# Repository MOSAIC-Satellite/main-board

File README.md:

# Main Board

This is the repository for MOSAIC's Main Board.

For detailed information on the Main Board, check out its core documentation [here](https://www.mosaicsat.org/core_documentation/hardware/main_board/).

To get your own MOSAIC Main Board, visit the MOSAIC fabrication guide [here](https://www.mosaicsat.org/getting_mosaic/).

## Current Features

*Newest board version: 1.0*

| **Feature** |
| :----------- |
| Swappable Processor Slot |
| 2x Expandable Memory Slots |
| 2x Function Board Slots |
| USB/Battery Voltage Regulator |
| Qwiic Voltage Regulator |
| Built-in Resettable PTC Fuse |
| 2-Pin JST Connector |
| Single Cell LiPo Charge Circuit |
| USB Type C Connector |
| 2x Qwiic Connectors |
| SWD 2x5 Header |
| Multiplexer for UART1  |
| Boot and Reset Buttons |
| 3x I/O switches |

## Planned Changes

The following are the current plans for changes to MOSAIC's Main Board. 

- Remove one of the expandable memory slots and replace it with a permanent SD card slot. This means that those interested only in SD cards for memory storage don't need a separate PCB to add to the board. 

## Change Log

You can find the change log for the Main Board on MOSAIC's website [here](https://www.mosaicsat.org/core_documentation/hardware/main_board/change_log/).

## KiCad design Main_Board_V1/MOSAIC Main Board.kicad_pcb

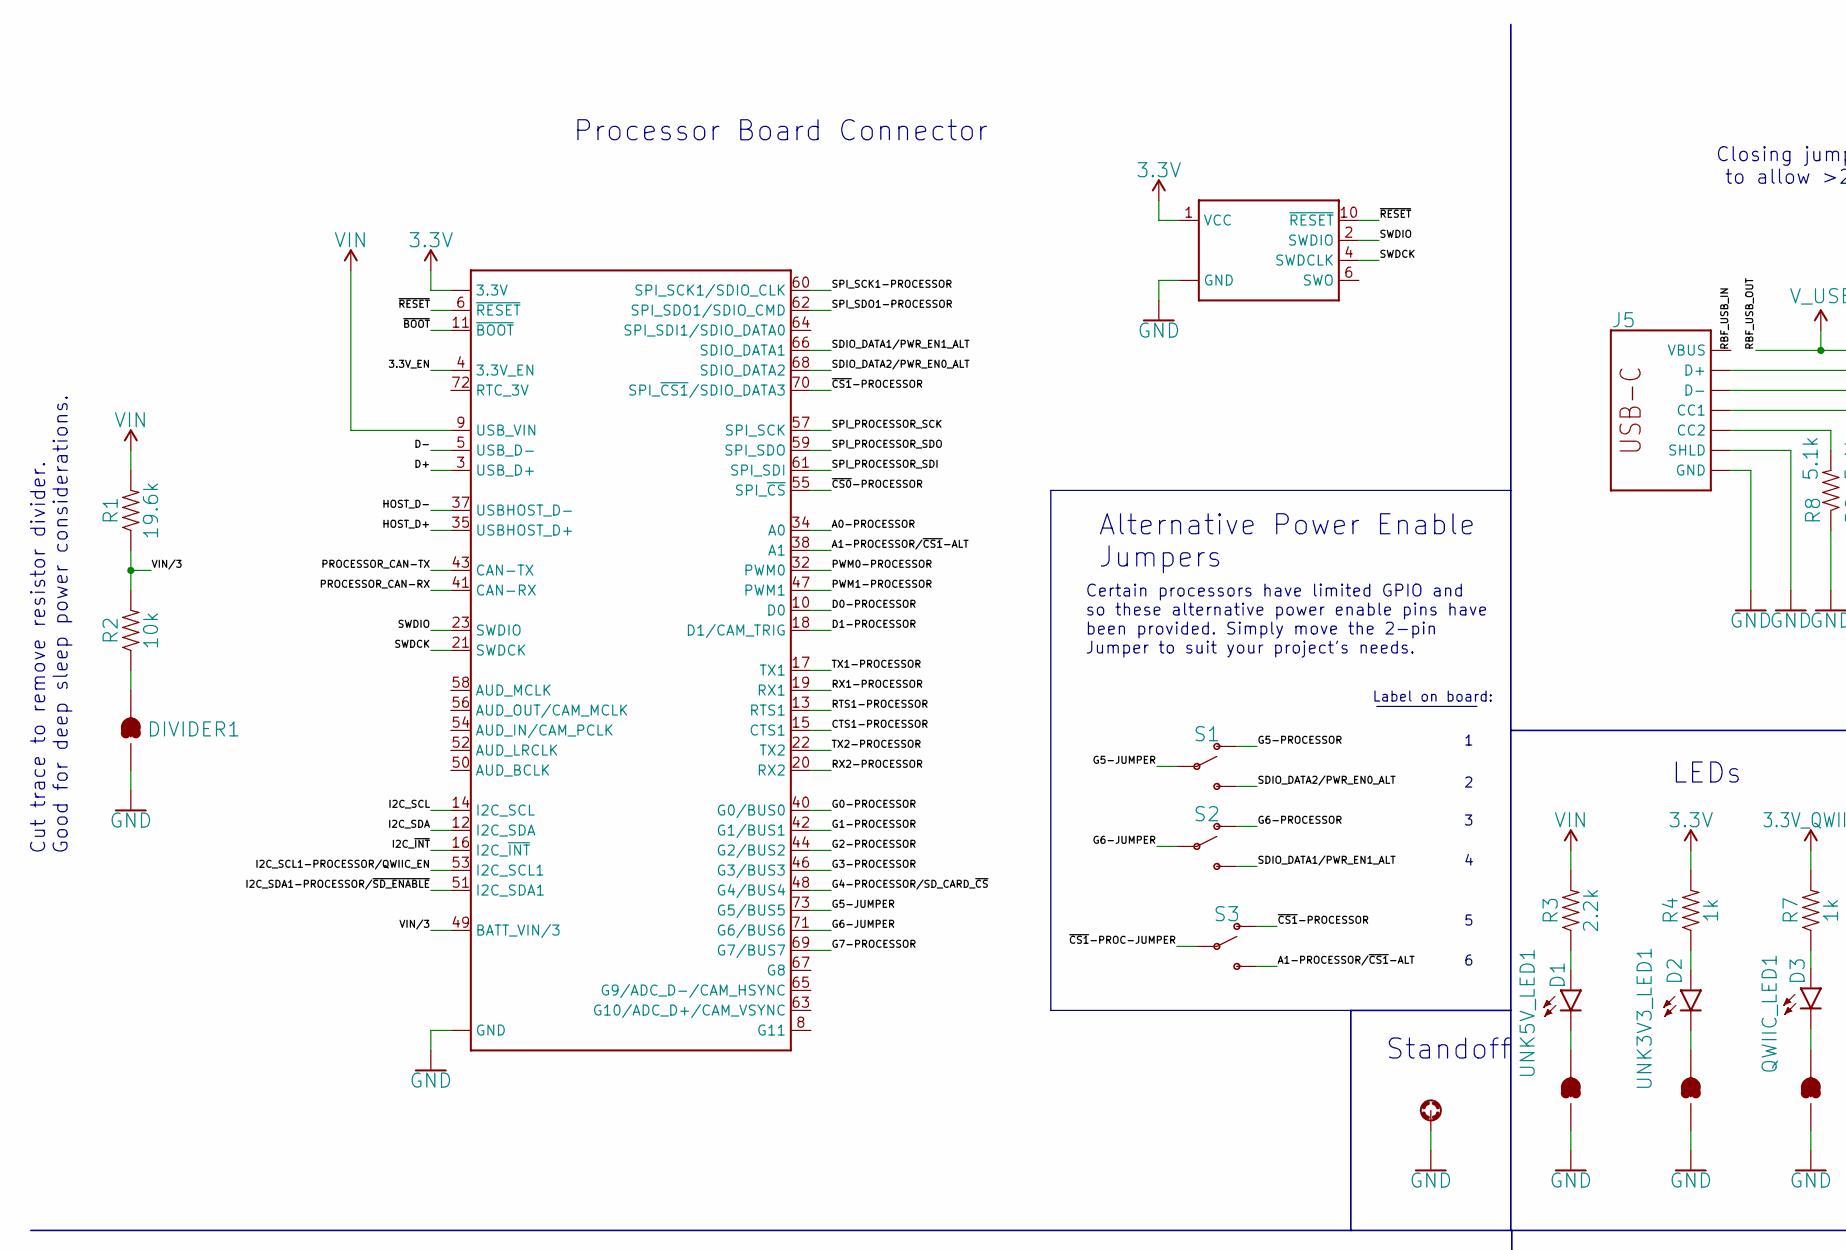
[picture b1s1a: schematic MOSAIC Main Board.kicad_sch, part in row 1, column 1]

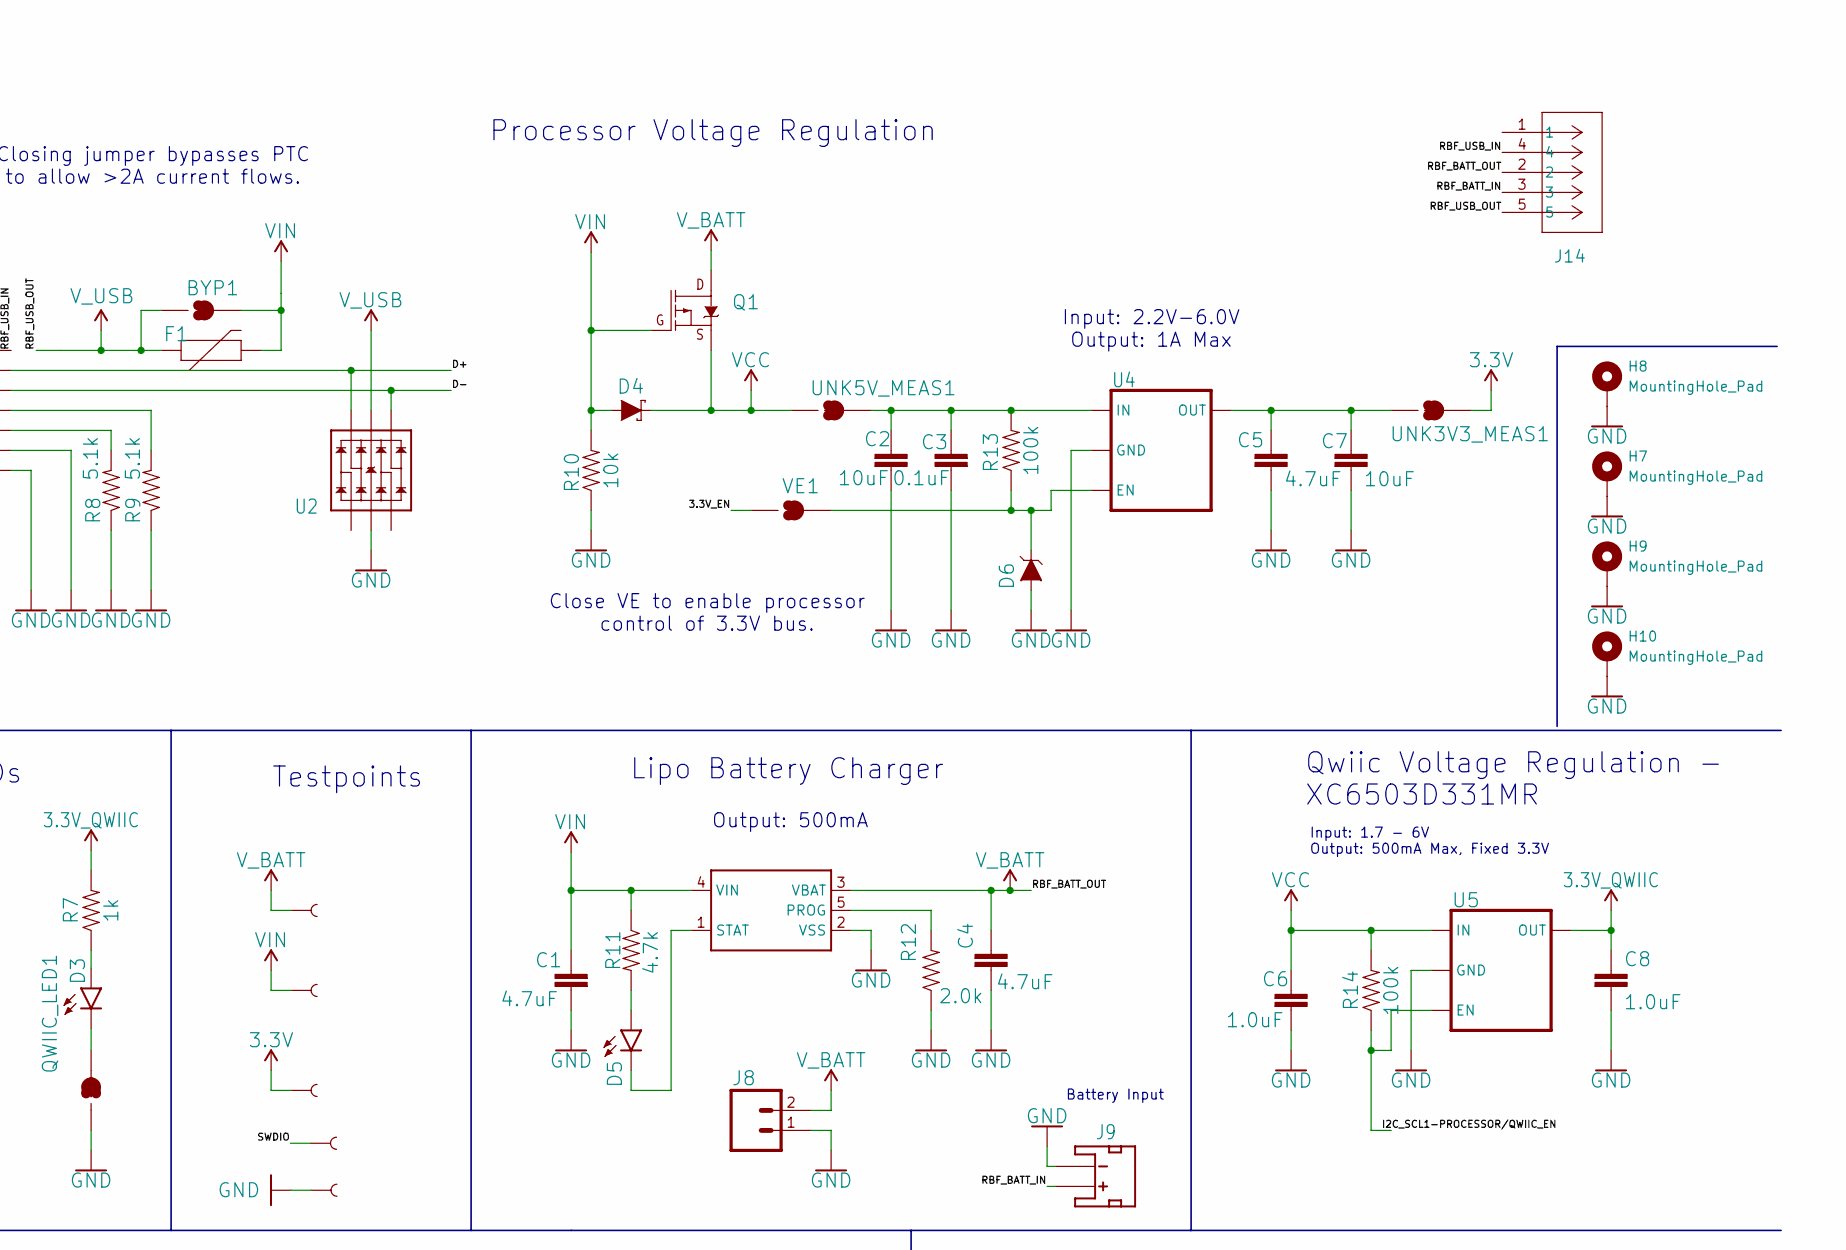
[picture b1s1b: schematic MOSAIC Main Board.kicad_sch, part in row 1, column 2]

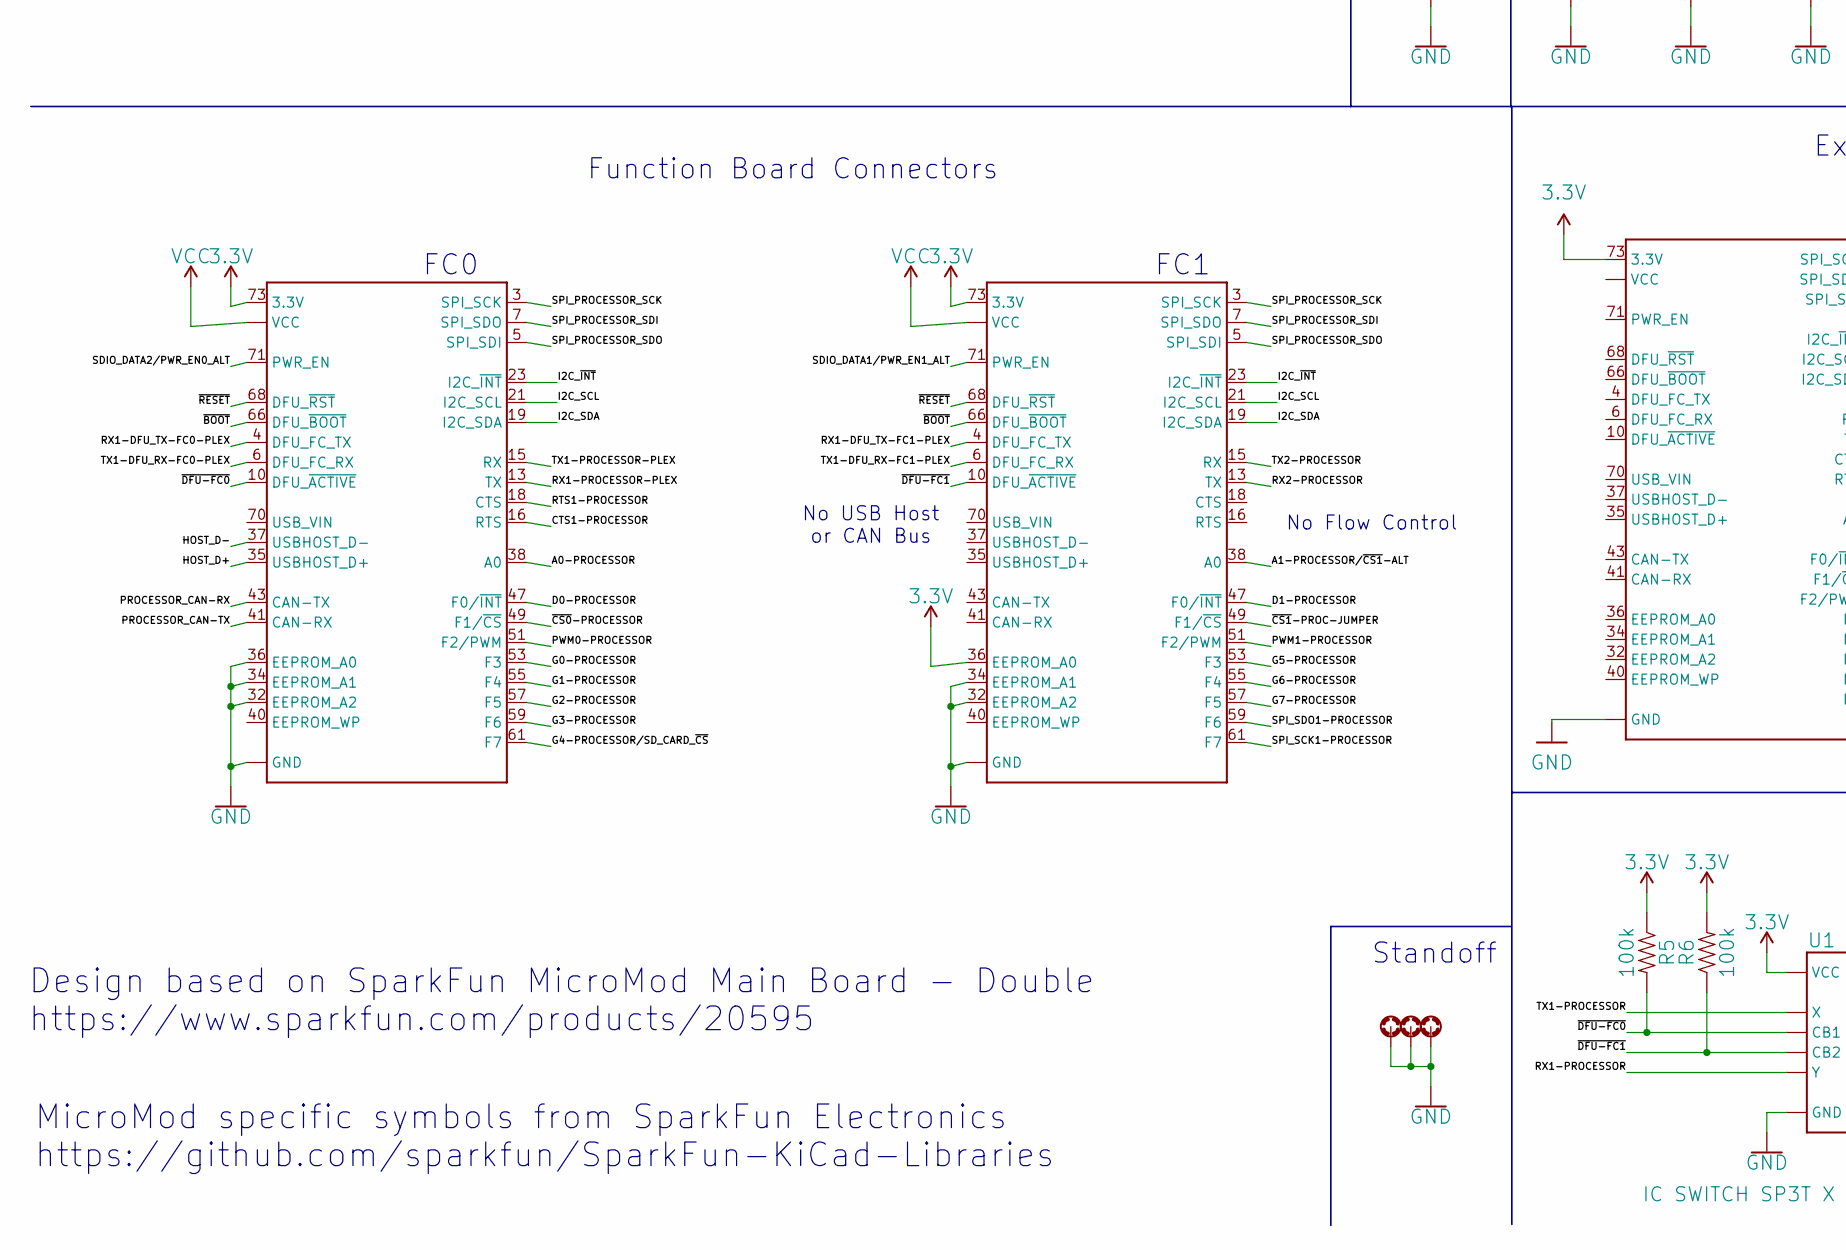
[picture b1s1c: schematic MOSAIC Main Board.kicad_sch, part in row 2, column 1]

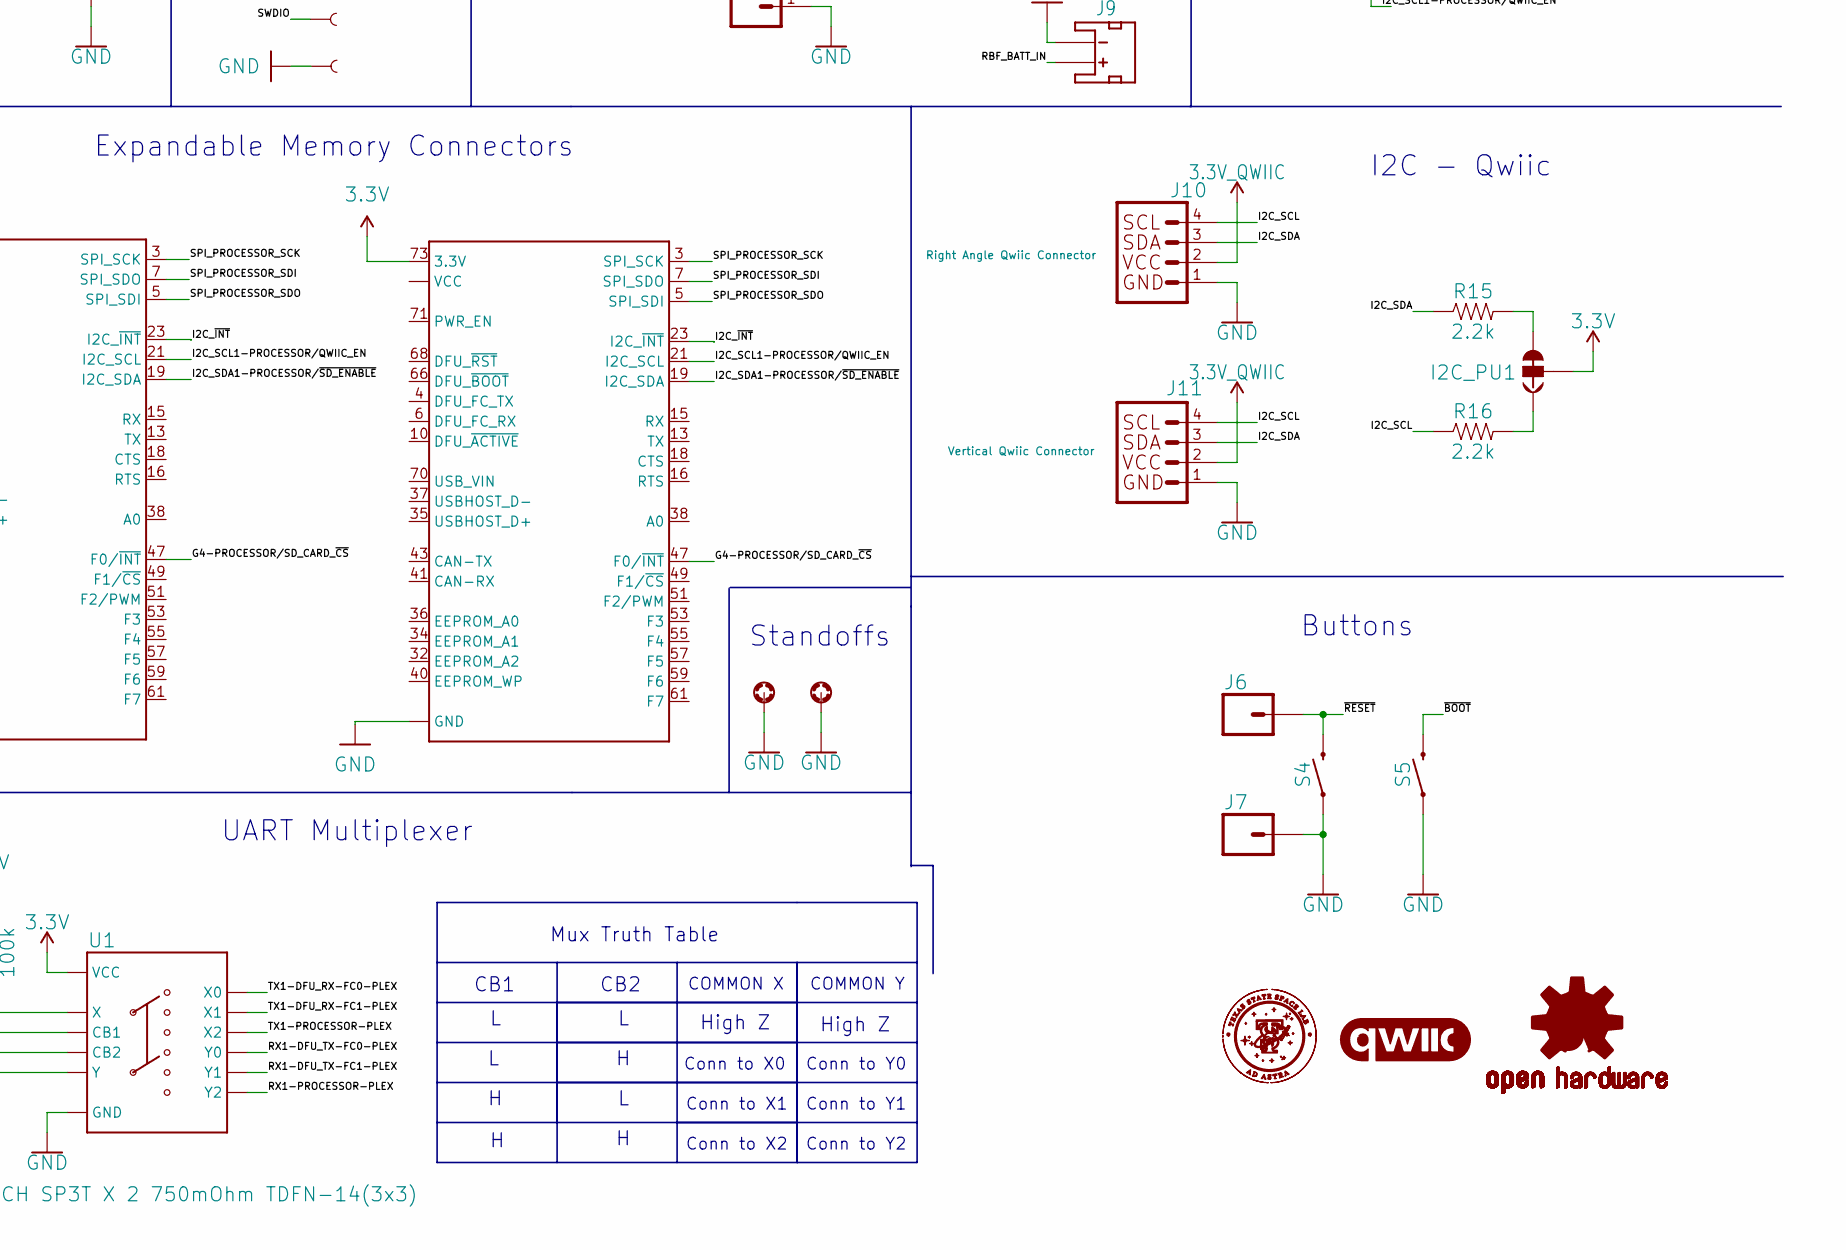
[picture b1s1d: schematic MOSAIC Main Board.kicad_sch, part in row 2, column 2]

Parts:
3.3V1: PAD.03X.05
BYP1: SMT-JUMPER_2_NO_SILK
C1, C4, C5: 4.7uF; 0603; JLCPCB Part # C1705
C2, C7: 10uF; 0805; JLCPCB Part # C318695
C3: 0.1uF; 0805; JLCPCB Part # C20617880
C6, C8: 1.0uF; 0603; JLCPCB Part # C1592
D1, D2, D3: LED RED CLEAR SMD; LED-0603; JLCPCB Part # C125099
D4: DIODE SCHOTTKY 40V 3A SMA; SMA-DIODE; JLCPCB Part # C85098
D5: LED YELLOW CLEAR CHIP SMD; LED-0603; JLCPCB Part # C125095
D6: SOD-323, 3.3V, 0.3W; SOD-323; JLCPCB Part # C550557
DIVIDER1: SMT-JUMPER_2_NC_TRACE_SILK
F1: PTC RESET FUSE 6V 2A 1210; 1210; JLCPCB Part # C135353
GND1: PAD.03X.05
H1, H2, H3, H4, H5, H6: STAND-OFF-REFLOW-M2.5_2.5MM_TALL; STAND-OFF-REFLOW-M2.5
H7, H8: MountingHole_Pad; MountingHole_3.2mm_M3_Pad
H9, H10: MountingHole_Pad; MountingHole_3.2mm_Pad_Oval
I2C_PU1: SMT-JUMPER_3_2-NC_TRACE_SILK
J1, J3: CONN E; M.2-CONNECTOR-E-FUNCTION-STANDARD; JLCPCB Part # C2977809
J2: CONN E; M.2-CONNECTOR-E; JLCPCB Part # C2977809
J4: CONN HEADER VERT 10POS 1.27MM; 2X5-PTH-1.27MM
J5: USB TYPE C R/A SMT 16PIN; USB TYPE C RA SMT 16PIN 10155435-00011LF_AMP; JLCPCB Part # C5409177
J6, J7: 1X01_NO_SILK
J8: 1X02_NO_SILK
J9: CONN_JST_BATT; JST-2-SMD; JLCPCB Part # C47647
J10: Right Angle Qwiic Connector; JST04_1MM_RA; JLCPCB Part # C7527619
J11: Vertical Qwiic Connector; JST04_1MM_VERT; JLCPCB Part # C160390
J12, J13: CONN E; M.2-CONNECTOR-E-Memory; JLCPCB Part # C2977809
J14: 35RAPC4BH3 CONN 3.5MM; CONN_35RAPC4BH3_SWC
LOGO1: QWIIC_LOGO_8MM; QWIIC_8MM
LOGO2: OSHW-LOGOL; OSHW-LOGO-L
Q1: MOSFET P-CH 30V 3.1A SOT23-3; SOT23-3; JLCPCB Part # C144996
QWIIC_LED1: SMT-JUMPER_2_NC_TRACE_SILK
R1: 19.6k; 0603; JLCPCB Part # C22898
R2, R10: 10k; 0603; JLCPCB Part # C840630
R3, R15, R16: 2.2k; 0603; JLCPCB Part # C163872
R4, R7: 1k; 0603; JLCPCB Part # C2484712
R5, R6, R13, R14: 100k; 0603; JLCPCB Part # C237115
R8, R9: 5.1k; 0603; JLCPCB Part # C14677
R11: 4.7k; 0603; JLCPCB Part # C4293273
R12: 2.0k; 0603; JLCPCB Part # C2076433
S1, S2, S3: switch; SW-SMD_SSSS810701; JLCPCB Part # C97433
S4, S5: SMD Switch 5.2mm; TACTILE_SWITCH_SMD_5.2MM; JLCPCB Part # C10852
SWDIO1: PAD.03X.05
U1: IC SWITCH SP3T X 2 750mOhm TDFN-14(3x3); TDFN-14-1EP_3x3mm_P0.4mm_EP1.78x2.35mm; JLCPCB Part # C1522710
U2: TVS DIODE 3.3VWM 6VC SOT26; SOT-23-6; JLCPCB Part # C531179
U3: MCP73831 IC BATT CNTL; SOT23-5; JLCPCB Part # C424093
U4: IC REG LINEAR 3.3V 1A 8UDFN; UDFN-8; JLCPCB Part # C151007
U5: XC6503D331MR-500mA-3.3V; SOT25; JLCPCB Part # C2891277
UNK3V3_LED1, UNK5V_LED1: SMT-JUMPER_2_NC_TRACE_SILK
UNK3V3_MEAS1, UNK5V_MEAS1: COMBO-JUMPER_2_NC_TRACE
VE1: SMT-JUMPER_2_NO_SILK
VIN1: PAD.03X.05
V_BATT1: PAD.03X.05

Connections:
3.3V: 3.3V1.1, I2C_PU1.2, J1.73 (3.3V), J2.2 (3.3V), J2.74 (3.3V), J3.36 (EEPROM_A0), J3.73 (3.3V), J4.1 (VCC), J12.73 (3.3V), J13.73 (3.3V), R4.2, R5.1, R6.2, U1.1 (VCC), UNK3V3_MEAS1.2, UNK3V3_MEAS1.4 (2)
3.3V_QWIIC: C8.1, J10.2, J11.2, R7.2, U5.5 (OUT)
/3.3V_EN: J2.4 (3.3V_EN), VE1.1
/A0-PROCESSOR: J1.38 (A0), J2.34 (A0)
/CTS1-PROCESSOR: J1.16 (RTS), J2.15 (CTS1)
/D0-PROCESSOR: J1.47 (F0/~INT), J2.10 (D0)
/D1-PROCESSOR: J2.18 (D1/CAM_TRIG), J3.47 (F0/~INT)
/D+: J2.3 (USB_D+), J5.A6 (D+), J5.B6 (D+), U2.6 (IO4)
/D-: J2.5 (USB_D-), J5.A7 (D-), J5.B7 (D-), U2.4 (IO3)
/G0-PROCESSOR: J1.53 (F3), J2.40 (G0/BUS0)
/G1-PROCESSOR: J1.55 (F4), J2.42 (G1/BUS1)
/G2-PROCESSOR: J1.57 (F5), J2.44 (G2/BUS2)
/G3-PROCESSOR: J1.59 (F6), J2.46 (G3/BUS3)
/G4-PROCESSOR/SD_CARD_~CS: J1.61 (F7), J2.48 (G4/BUS4), J12.47 (F0/~INT), J13.47 (F0/~INT)
/G5-JUMPER: J2.73 (G5/BUS5), S1.2
/G5-PROCESSOR: J3.53 (F3), S1.1 (O)
/G6-JUMPER: J2.71 (G6/BUS6), S2.2
/G6-PROCESSOR: J3.55 (F4), S2.1 (O)
/G7-PROCESSOR: J2.69 (G7/BUS7), J3.57 (F5)
/HOST_D+: J1.35 (USBHOST_D+), J2.35 (USBHOST_D+)
/HOST_D-: J1.37 (USBHOST_D-), J2.37 (USBHOST_D-)
/I2C_SCL: J1.21 (I2C_SCL), J2.14 (I2C_SCL), J3.21 (I2C_SCL), J10.4, J11.4, R16.1
/I2C_SCL1-PROCESSOR/QWIIC_EN: J2.53 (I2C_SCL1), J12.21 (I2C_SCL), J13.21 (I2C_SCL), R14.1, U5.3 (EN)
/I2C_SDA: J1.19 (I2C_SDA), J2.12 (I2C_SDA), J3.19 (I2C_SDA), J10.3, J11.3, R15.1
/I2C_SDA1-PROCESSOR/~SD_ENABLE: J2.51 (I2C_SDA1), J12.19 (I2C_SDA), J13.19 (I2C_SDA)
/I2C_~INT: J1.23 (I2C_~INT), J2.16 (I2C_~INT), J3.23 (I2C_~INT), J12.23 (I2C_~INT), J13.23 (I2C_~INT)
/PROCESSOR_CAN-RX: J1.43 (CAN-TX), J2.41 (CAN-RX)
/PROCESSOR_CAN-TX: J1.41 (CAN-RX), J2.43 (CAN-TX)
/PWM0-PROCESSOR: J1.51 (F2/PWM), J2.32 (PWM0)
/PWM1-PROCESSOR: J2.47 (PWM1), J3.51 (F2/PWM)
/RBF_BATT_IN: J9.2 (+), J14.3
/RBF_USB_IN: J5.VBUS1 (VBUS), J5.VBUS2 (VBUS), J14.4
/RTS1-PROCESSOR: J1.18 (CTS), J2.13 (RTS1)
/RX1-DFU_TX-FC0-PLEX: J1.4 (DFU_FC_TX), U1.9 (Y0)
/RX1-DFU_TX-FC1-PLEX: J3.4 (DFU_FC_TX), U1.11 (Y1)
/RX1-PROCESSOR: J2.19 (RX1), U1.14 (Y)
/RX1-PROCESSOR-PLEX: J1.13 (TX), U1.12 (Y2)
/RX2-PROCESSOR: J2.20 (RX2), J3.13 (TX)
/SDIO_DATA2/PWR_EN0_ALT: J1.71 (PWR_EN), J2.68 (SDIO_DATA2), S1.3 (S)
/SPI_PROCESSOR_SCK: J1.3 (SPI_SCK), J2.57 (SPI_SCK), J3.3 (SPI_SCK), J12.3 (SPI_SCK), J13.3 (SPI_SCK)
/SPI_PROCESSOR_SDI: J1.7 (SPI_SDO), J2.61 (SPI_SDI), J3.7 (SPI_SDO), J12.7 (SPI_SDO), J13.7 (SPI_SDO)
/SPI_PROCESSOR_SDO: J1.5 (SPI_SDI), J2.59 (SPI_SDO), J3.5 (SPI_SDI), J12.5 (SPI_SDI), J13.5 (SPI_SDI)
/SPI_SCK1-PROCESSOR: J2.60 (SPI_SCK1/SDIO_CLK), J3.61 (F7)
/SPI_SDO1-PROCESSOR: J2.62 (SPI_SDO1/SDIO_CMD), J3.59 (F6)
/SWDCK: J2.21 (SWDCK), J4.4 (SWDCLK)
/SWDIO: J2.23 (SWDIO), J4.2 (SWDIO), SWDIO1.1
/TX1-DFU_RX-FC0-PLEX: J1.6 (DFU_FC_RX), U1.7 (X0)
/TX1-DFU_RX-FC1-PLEX: J3.6 (DFU_FC_RX), U1.5 (X1)
/TX1-PROCESSOR: J2.17 (TX1), U1.2 (X)
/TX1-PROCESSOR-PLEX: J1.15 (RX), U1.4 (X2)
/TX2-PROCESSOR: J2.22 (TX2), J3.15 (RX)
/VIN/3: J2.49 (BATT_VIN/3), R1.1, R2.2
/~BOOT: J1.66 (DFU_~BOOT), J2.11 (~BOOT), J3.66 (DFU_~BOOT), S5.3 (2), S5.4 (2)
/~CS0-PROCESSOR: J1.49 (F1/~CS), J2.55 (SPI_~CS)
/~CS1-PROC-JUMPER: J3.49 (F1/~CS), S3.2
/~CS1-PROCESSOR: J2.70 (SPI_~CS1/SDIO_DATA3), S3.1 (O)
/~DFU-FC0: J1.10 (DFU_~ACTIVE), R5.2, U1.6 (CB1)
/~DFU-FC1: J3.10 (DFU_~ACTIVE), R6.1, U1.13 (CB2)
/~RESET: J1.68 (DFU_~RST), J2.6 (~RESET), J3.68 (DFU_~RST), J4.10 (~RESET), J6.1, S4.3 (2), S4.4 (2)
GND: C1.2, C2.2, C3.2, C4.2, C5.2, C6.2, C7.2, C8.2, D6.A, DIVIDER1.1, GND1.1, H1.1, H2.1, H3.1, H4.1, H5.1, H6.1, H7.1, H8.1, H9.1, H10.1, J1.1 (GND), J1.2 (GND), J1.8 (GND), J1.32 (EEPROM_A2), J1.33 (GND), J1.34 (EEPROM_A1), J1.36 (EEPROM_A0), J1.39 (GND), J1.45 (GND), J1.75 (GND), J2.1 (GND), J2.7 (GND), J2.33 (GND), J2.36 (GND), J2.39 (GND), J2.45 (GND), J2.75 (GND), J3.1 (GND), J3.2 (GND), J3.8 (GND), J3.32 (EEPROM_A2), J3.33 (GND), J3.34 (EEPROM_A1), J3.39 (GND), J3.45 (GND), J3.75 (GND), J4.3 (GND), J4.5 (GND), J4.9 (GND), J5.GND, J5.GND2 (GND), J5.SHLD1 (SHLD), J5.SHLD2 (SHLD), J5.SHLD3 (SHLD), J5.SHLD4 (SHLD), J7.1, J8.1, J9.1 (-), J10.1, J11.1, J12.1 (GND), J12.2 (GND), J12.8 (GND), J12.33 (GND), J12.39 (GND), J12.45 (GND), J12.75 (GND), J13.1 (GND), J13.2 (GND), J13.8 (GND), J13.33 (GND), J13.39 (GND), J13.45 (GND), J13.75 (GND), QWIIC_LED1.1, R8.1, R9.1, R10.1, R12.1, S4.1, S4.2 (1), S5.1, S5.2 (1), U1.8 (GND), U2.2 (VSS), U3.2 (VSS), U4.4 (GND), U4.EP (GND), U5.2 (GND), UNK3V3_LED1.1, UNK5V_LED1.1
unnamed: D1.A, R3.1
unnamed: D1.C, UNK5V_LED1.2
unnamed: D2.A, R4.1
unnamed: D2.C, UNK3V3_LED1.2
unnamed: D3.A, R7.1
unnamed: D3.C, QWIIC_LED1.2
unnamed: D5.A, R11.2
unnamed: DIVIDER1.2, R2.1
unnamed: I2C_PU1.1, R16.2
unnamed: I2C_PU1.3, R15.2
unnamed: J5.A5 (CC1), R9.2
unnamed: J5.B5 (CC2), R8.2
unnamed: J12.72 (VCC), J12.74 (VCC)
unnamed: J13.72 (VCC), J13.74 (VCC)
unnamed: R12.2, U3.5 (PROG)
unnamed: D5.C, U3.1 (STAT)
unnamed: D6.C, R13.1, U4.5 (EN), VE1.2
unnamed: C2.1, C3.1, R13.2, U4.8 (IN), UNK5V_MEAS1.2, UNK5V_MEAS1.4 (2)
unnamed: C5.1, C7.1, U4.1 (OUT), UNK3V3_MEAS1.1, UNK3V3_MEAS1.3 (1)
VCC: C6.1, D4.C, J1.72 (VCC), J1.74 (VCC), J3.72 (VCC), J3.74 (VCC), Q1.2 (S), R14.2, U5.1 (IN), UNK5V_MEAS1.1, UNK5V_MEAS1.3 (1)
VIN: BYP1.2, C1.1, D4.A, F1.2, J2.9 (USB_VIN), Q1.1 (G), R1.2, R3.2, R10.2, R11.1, U3.4 (VIN), VIN1.1
V_BATT: C4.1, J8.2, J14.2, Q1.3 (D), U3.3 (VBAT), V_BATT1.1
V_USB: BYP1.1, F1.1, J14.5, U2.5 (VCC)

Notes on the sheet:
Label on board:
FC1
Function Board Connectors
Conn to X2
Design based on SparkFun MicroMod Main Board - Double https://www.sparkfun.com/products/20595
Battery Input
I2C - Qwiic
Standoff
Mux Truth Table
Processor Voltage Regulation
Conn to Y1
High Z
Conn to Y2
Conn to Y0
Processor Board Connector
No Flow Control
MicroMod specific symbols from SparkFun Electronics https://github.com/sparkfun/SparkFun-KiCad-Libraries
Testpoints
Input: 1.7 - 6V Output: 500mA Max, Fixed 3.3V
Lipo Battery Charger
FC0
Output: 500mA
Cut trace to remove resistor divider. Good for deep sleep power considerations.
Close VE to enable processor control of 3.3V bus.
Buttons
Expandable Memory Connectors
Alternative Power Enable Jumpers
CB2
UART Multiplexer
COMMON Y
Certain processors have limited GPIO and so these alternative power enable pins have been provided. Simply move the 2-pin Jumper to suit your project's needs.
Input: 2.2V-6.0V Output: 1A Max
Conn to X0
LEDs
Closing jumper bypasses PTC to allow >2A current flows.
Conn to X1
No USB Host or CAN Bus
CB1
COMMON X
Standoffs

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
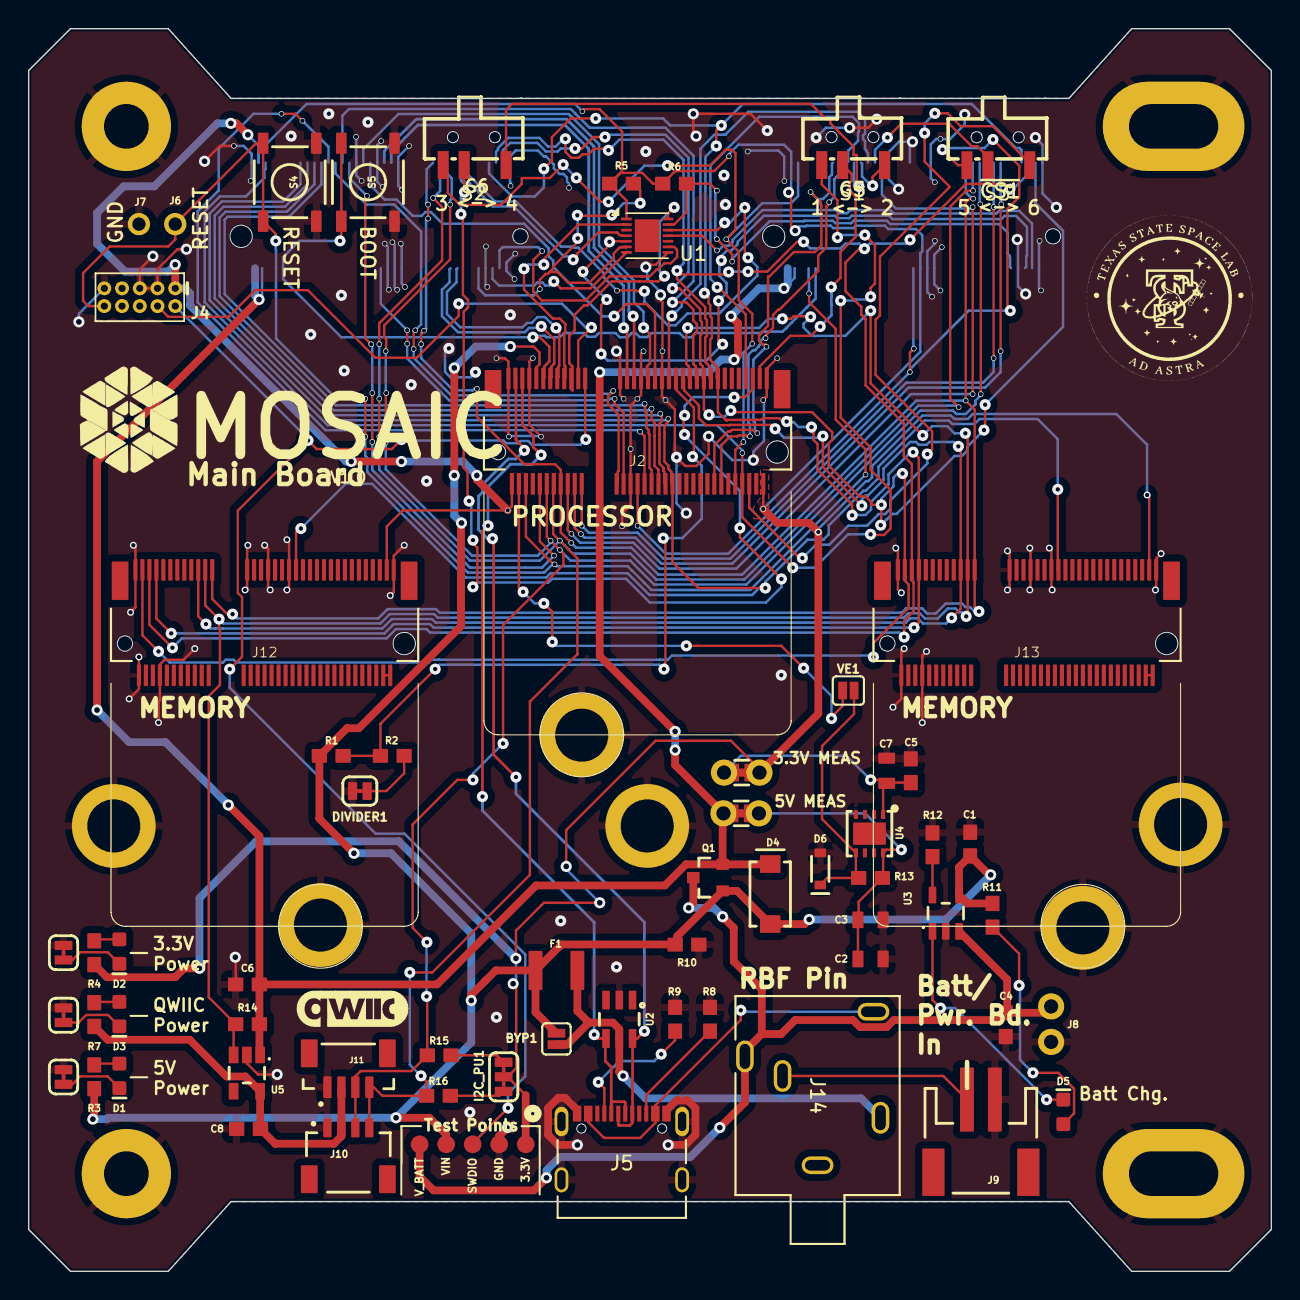
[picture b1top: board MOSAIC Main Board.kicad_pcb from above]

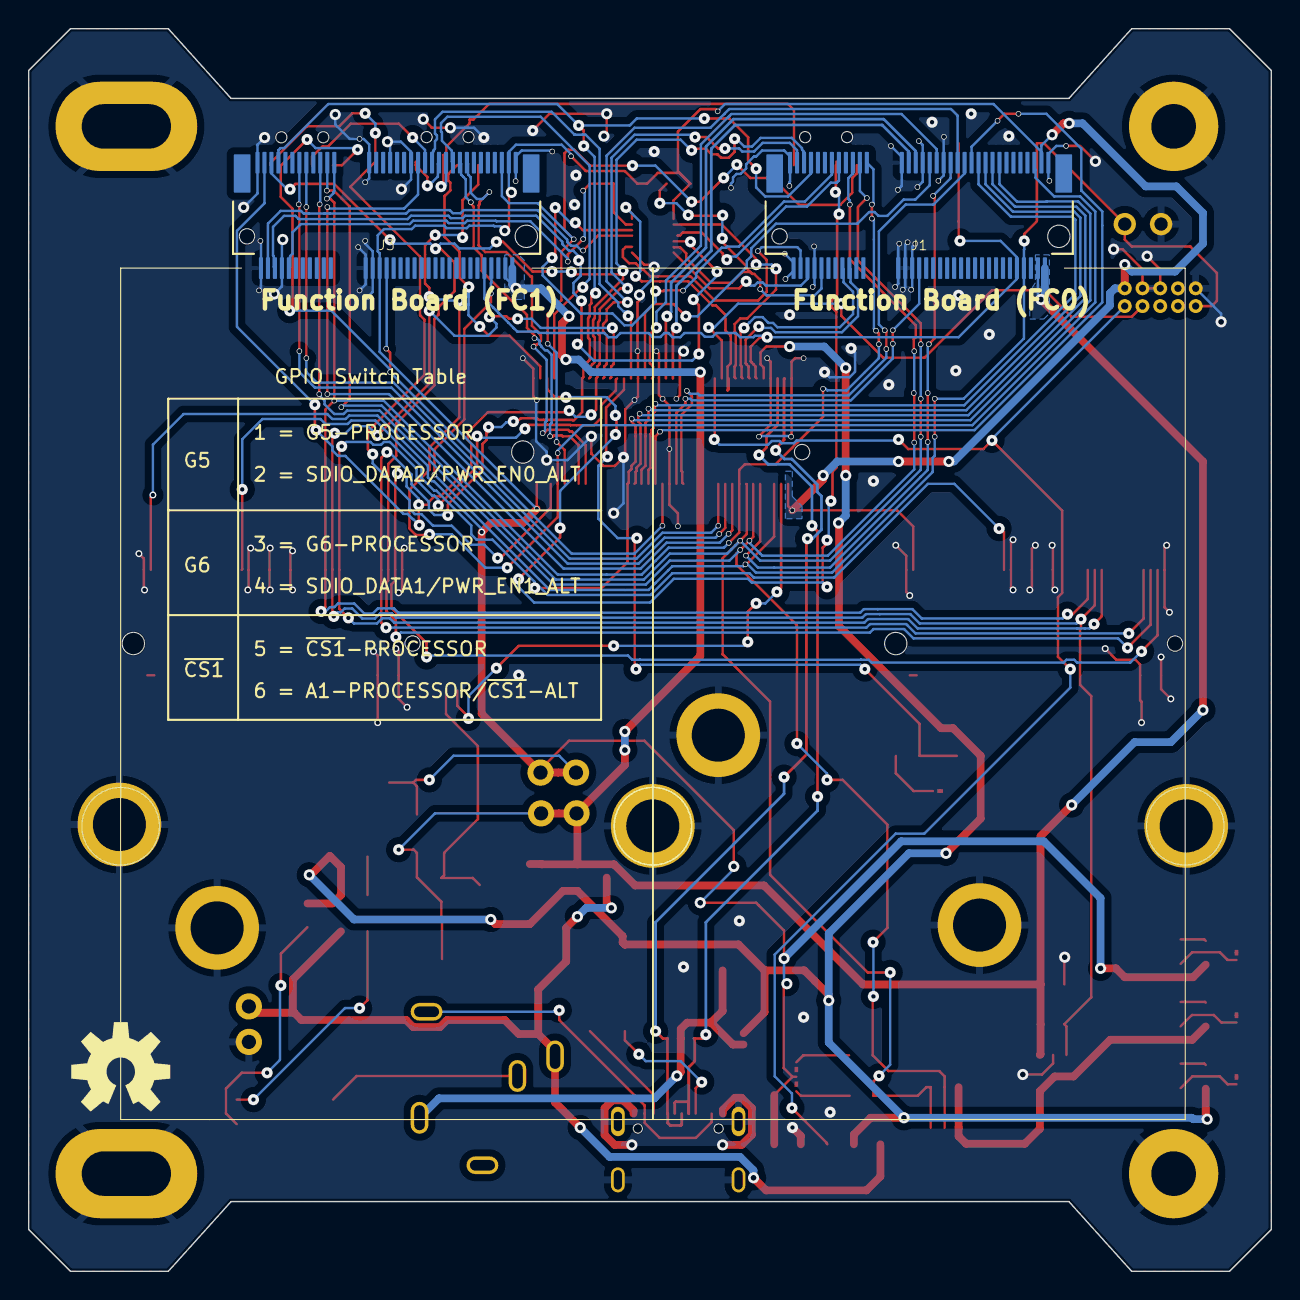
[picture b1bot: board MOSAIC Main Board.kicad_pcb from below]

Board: 2 copper layers, 89.0 x 89.0 mm, 82 parts (6 on the bottom side), 85 nets.

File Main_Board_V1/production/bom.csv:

Designator,Footprint,Quantity,Value,LCSC Part #
"C1, C4, C5",0603,3,4.7uF,C1705
"C2, C7",0805,2,10uF,C318695
C3,0805,1,0.1uF,C20617880
"C6, C8",0603,2,1.0uF,C1592
"D1, D2, D3",LED-0603,3,LED RED CLEAR SMD,C125099
D4,SMA-DIODE,1,DIODE SCHOTTKY 40V 3A SMA,C85098
D5,LED-0603,1,LED YELLOW CLEAR CHIP SMD,C125095
D6,SOD-323,1,"SOD-323, 3.3V, 0.3W",C550557
F1,1210,1,PTC RESET FUSE 6V 2A 1210,C135353
"J1, J3",M.2-CONNECTOR-E-FUNCTION-STANDARD,2,CONN E,C2977809
J10,JST04_1MM_RA,1,Right Angle Qwiic Connector,C7527619
J11,JST04_1MM_VERT,1,Vertical Qwiic Connector,C160390
"J12, J13",M.2-CONNECTOR-E-Memory,2,CONN E,C2977809
J2,M.2-CONNECTOR-E,1,CONN E,C2977809
J5,USB TYPE C RA SMT 16PIN 10155435-00011LF_AMP,1,USB TYPE C R/A SMT 16PIN,C5409177
J9,JST-2-SMD,1,CONN_JST_BATT,C47647
Q1,SOT23-3,1,MOSFET P-CH 30V 3.1A SOT23-3,C144996
R1,0603,1,19.6k,C22898
"R10, R2",0603,2,10k,C840630
R11,0603,1,4.7k,C4293273
R12,0603,1,2.0k,C2076433
"R13, R14, R5, R6",0603,4,100k,C237115
"R15, R16, R3",0603,3,2.2k,C163872
"R4, R7",0603,2,1k,C2484712
"R8, R9",0603,2,5.1k,C14677
"S1, S2, S3",SWITCH_SPST_SMD_A,3,switch,C19188866
"S4, S5",TACTILE_SWITCH_SMD_5.2MM,2,SMD Switch 5.2mm,C10852
U1,TDFN-14-1EP_3x3mm_P0.4mm_EP1.78x2.35mm,1,IC SWITCH SP3T X 2 750mOhm TDFN-14(3x3),C1522710
U2,SOT-23-6,1,TVS DIODE 3.3VWM 6VC SOT26,C531179
U3,SOT23-5,1,MCP73831 IC BATT CNTL,C424093
U4,UDFN-8,1,IC REG LINEAR 3.3V 1A 8UDFN,C151007
U5,SOT25,1,XC6503D331MR-500mA-3.3V,C2891277

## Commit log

2024-07-10 Initial Adding of Files
2025-04-16 Updated files from KiCAD 7.0 to 9.0
2025-04-16 Created board outline drawing
    Created the outline drawing for the new, standardized, board outline.
2025-04-16 Updated schematic from KiCAD 7.0 to 9.0
2025-04-16 Changed schematic rev number
2025-04-16 Revert back to fix bug
2025-04-16 Finish editing for now
2025-04-16 Added new board cutout and m3 mount holes
2025-04-16 Made new board cutout and added m3 mount holes.
2025-04-16 Moved stuff around
2025-04-29 Updated component sourcing
    For C2 and C3
2025-04-29 Updated source for R2
2025-04-29 Updated source for R12
2025-04-29 Updated source for J9
2025-04-29 Updated source J14
2025-04-29 Updated source for U2
2025-04-30 Updated footprint for S1
2025-04-30 Updated measurements for board outline
2025-04-30 Added ground plane to new board outline
2025-04-30 Deleted old tracks and started organizing surface components
2025-04-30 Create #auto_saved_files#
2025-04-30 Updated net class rules
2025-04-30 Finished session
2025-05-05 Wired/Placed processor/x2 module connectors
2025-05-28 Lots of placements and routing
2025-05-28 Finished session.
2025-05-29 More placement and routing work
2025-05-29 More placement and routing
2025-05-30 Placement and routing
2025-05-30 Small correction
2025-06-13 Changed user.1 to user.5
2025-06-13 Updating JLCPCB sources
2025-06-13 updating JLCPCB comp sources
2025-06-13 add jlcpcb comp sources
2025-06-13 added jlcpcb comp sources
2025-06-13 finished comp sourcing
2025-06-14 Finish comp placement
2025-06-14 started JLCPCB setup
2025-06-14 Finished JLCPCB setup
2025-06-16 added bom
    Added bom for assembly after JLCPCB assembly.
2025-06-23 small edits
2025-06-23 fixed jlcpcb comp placement
2025-06-24 minor changes to text sizing
2025-06-24 board text adjustments
2025-06-26 small changes
2025-06-26 Started adding 3d models
2025-07-12 fix batt input
2025-07-16 added switch table to back
2025-07-17 new production folder
2025-07-24 new production file
2025-07-29 added new html BOM
2026-01-04 labeled the fc board slots
2026-01-04 added more labels
2026-01-05 replaced out of stock switches
2026-01-09 Made new fab files
    Made new fabrication files for JLCPCB production that include the most recent changes to the board.
2026-01-09 saved progress

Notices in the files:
Main_Board_V1/MOSAIC Main Board.kicad_pcb:
Copyright (c) 2022 - 2025
